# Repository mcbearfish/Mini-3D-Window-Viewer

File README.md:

# 3D Window Project

## About
This is a developmental project intended to refresh my skills on designing and programming an STM32 microcontroller board. I chose a project scope that I believed would provide difficult circuit and programming challenges. I will document the development process in this README.<br />

If you stumble across this project feel free to use it for educational purposes. If you find errors or have questions about the circuit design or code feel free to reach out. Please cite this repository as a source if you plan to use it.<br />

## Table of Contents
- [Project Description](#project-description)
- [Demo Video](#demo-video)
- [Hardware / Software Used](#hardware--software-used)
- [Circuit Design](#circuit-design)
- [Box Design](#box-design)
- [Code Design](#code-design)
- [Notes on AI Assistance](#notes-on-ai-assistance)
- [Final Result](#final-result)

## Project Description
This project is the 3D Window Viewer.<br />

When placed on a flat surface, the device on startup will create a window into a 3D scene of a hammer (Boiler Up and Hail Purdue!). After startup, tilting and rotating the device updates the view of a 3D hammer while the virtual position remains anchored.<br />

This project uses I2C accelerometer, gyroscope, and magnetometer sensors to estimate device orientation in C. The original goal was IMU-only position tracking, but drift made that impractical, so I redesigned the demo around constrained motion. <br />

I designed my own custom STM32 development board and sensor board using KiCad Schematic and PCB Design Software. <br />

## Demo Video

## Hardware / Software Used
- STM32 microcontroller
- Custom STM32 main PCB
- Custom sensor PCB
- Accelerometer, gyroscope, and magnetometer over I2C
- LCD display
- KiCad for schematic and PCB design
- CLion IDE
- C firmware

## Circuit Design
#### STM32 Circuit
<br />
This STM32 chip was chosen for its large number of GPIO pins and processing capabilities.

#### Button
<br />
Simple button circuit to test user inputs.

#### LEDs
<br />
Used for initial testing and debugging.

#### Crystal Oscillator
<br />
Provides a highly stable, accurate, and precise frequency reference.

#### USB-C Connector
<br />
Provides power to the board.

#### Boot Switch
<br />
Reset switch.

#### Mounting Holes
<br />
Grounded pads to use for mounting and probe testing.

#### Pin Connectors
<br />

#### Buck Converter
<br />
Chosen to smooth 5V to 3.3V for STM32 chip and sensors.

#### Accelerometer and Gyroscope
<br />
Chosen to estimate device orientation and motion. IMU-only position tracking was tested, but drift made it impractical for this version.

#### Magnetometer
<br />
Chosen to improve heading estimation and help correct gyro drift over time.

#### Pin Connector
<br />

#### Mounting Holes
<br />

#### Notes
I found Google's Gemini AI tool to be extremely helpful during this design process. Especially with mapping the pinout of the display to STM32. I used a cheap knockoff with no documentation and poor pinout labels. In the future may need to remap pins if display fails to work. See ARSensors project for second Board meant to connect sensors to this main board.<br />

Manufacturing files can be found for each board in this repository.<br />

#### Main PCB
<br />

<br />

<br />

<br />

#### Sensors PCB
<br />

<br />

<br />

<br />

#### Design Process
Designing my first board in almost 4 years was a great experience. In the workspace I have been living in a more software heavy environment. I found this project to be a great refresher of my skills.<br />

I found the initial research phase to be quite enjoyable and straightforward. I easily identified the types of sensors, display, and STM32 chip I thought would be capable for the performance I wanted. Now that I identified the key components it was time to begin creating the schematic.<br />

I quickly realized this was a larger challenge than my senior design project. Although I took a significant part in the circuit design, I realized how beneficial it was having a team of 4 people in multiple disciplines. The components I selected for this project were much more sophisticated than what was chosen for the senior design project. I was honestly a little overwhelmed at the start. I had to take my time and started to break components down. I started with the most important part, the STM32 chip. <br />

For the STM32 I first connected any power related pins and decoupling capacitors. Then I used the STM32CubeMX tool to assign pinouts. I knew between the display and other peripherals I needed a lot of pins, so I started by making sure the chip was capable of supporting them all. Once I verified the chip was capable I began connecting components. The most critical was the USB-C connector, which flashes code onto the chip. The USB-C will also provide power to the whole system. I spent quite a bit of time researching possible power designs. The USB-C provides 5V and I need 3.3V for the STM32 and sensors. I eventually decided on a synchronous buck converter because it would provide an efficient and stable step down from 5V to 3.3V. The display needs 5V, so I decided on a simple low-pass filter because it would provide a clean signal and I have experience with designing those on circuit boards in the past.<br />

Next I added the sensors. I found the datasheets to be extremely helpful. The design process was made much easier by following the typical application circuits that they detailed. Then I added the display, button, and some LEDs. The extra LEDs and button will be useful at the start of programming to make sure the board can properly run code and debug. Lastly I added a connector for debug pins.<br />

Now that I had a schematic to follow I moved onto the PCB layout. This portion was much more difficult than expected. It was at this point I had to take into account physical and cost restrictions. JLCPCB was my choice of board manufacturer. To minimize costs I decided on a 2 layer board, which gave me a lot of physical trace constraints.  Also, since the sensors are a bit costly, I decided to move them to a second circuit board to save on future costs. With these new challenges I had to go back to my schematic and STM32CubeMX. Unfortunately I was not able to place my STM32 pinouts more conveniently to minimize trace crossovers. At this point I decided to go with a more generic pin layout that I can wire with some 2.54mm connectors to minimize my trace lengths and crossovers. In the future I will look at more layered boards or other STM32 chips as potential solutions.<br />

To minimize costs on JLCPCB I tried to identify basic parts in the JLCPCB library. Not all parts selected were in that and drove up the cost (~$3 per part not in the basic library). In the future I will place more emphasis on this to lower my costs.<br />

Major credit to Phil's Lab PCB Design video: https://www.youtube.com/watch?v=aVUqaB0IMh4. This was a great refresher on circuit board design and I highly recommend his channel.<br />

#### Soldering and Assembly
When ordering the board I decided that to save on costs to I would hand solder some of the components. This involved things the STM32 chip, USB-C connector, asynchronous buck converter, buttons, and pins. I felt this was a great skill refresher. I took it slow and steady. I started with easier items like the pins and buttons to get back into the flow of things. The picture below is from right before I went to solder the STM chip.<br />
<br />

I bought a cheap soldering station and found it pretty useful when adding the smaller components. In the picture below you can see a cheaper soldering iron. I found this ok for the larger components but, I decided it was safer to spend the money and get a proper iron for the delicate items like the USB-C and STM32 chip.<br />
<br />

### Box Design
I bought a simple project box and placed the main board inside the box. I left the sensor board on top along with the display to keep them on the same level.

## Code Design
#### Initial Project Scope
The initial goal of the project was to use the IMU sensors to track the 3D coordinates of the device so that it could act as a camera. The camera would then be able to view a 3D object fixed in space from all angles and get closer or farther away.<br />

#### Limitations of IMU Sensors
While prototyping I found that it was not feasible to use the IMU sensors alone for positional tracking. The significant position drift was too much to overcome, even with adjusting bias in the Kalman filter parameters. I also tested the individual sensors to check for noise and bias. Surprisingly, these cheaper sensors performed quite well. The accelerometer did display the most noise. I believe this was due to environmental sensitivities. Testing was performed on my desk and away from any electronics, this however does not guarantee a perfectly still environment. <br />

Since position is calculated by integrating acceleration twice, even with tiny errors, the positional data errors grew massive. The estimated position drifted so quickly that the 3D object would only remain visible for a split second. I determined this was unusable and decided to change scope. <br />

#### Redesign
I decided to pivot the project and try to get the most out of the current setup. I decided to simulate the camera view of the 3D object where moving and tilting the box changes camera view direction realistically, but position is anchored. <br />

#### Code Flow
The main program initializes the board, sensors, sensor fusion, and 3D engine before entering the main loop. In the loop, new sensor data is read and passed into the sensor fusion algorithm. This project uses an Extended Kalman Filter, which fuses gyroscope, accelerometer, and magnetometer data into a stable orientation estimate. That orientation estimate is then used to update the rendered 3D object and draw the pose overlay.<br />
```
main()
|
+-- HAL_Init()
+-- SystemClock_Config()
+-- MX_GPIO_Init()
+-- MX_FMC_Init()
+-- I2C_Bus_Reset()
+-- MX_I2C1_Init()
|
+-- Engine3D_Init()
|   \-- GPU_Init()
|
+-- Sensors_Init()
+-- Sensors_ShowStartupCountdown()
+-- Sensors_Calibrate()
+-- Sensors_ShowInstructionScreen()
+-- Sensors_GetReferenceFrame()
+-- EKF_Init()
+-- EKF_SetReference()
|
\-- while (1)
    +-- Sensors_Read()
    +-- EKF_Predict()
    +-- EKF_Update()
    +-- ComputeSpinCommands()
    +-- IntegrateQuat()
    +-- IsStableForReset()
    |   \-- maybe ResetObjectOrientation()
    +-- QuaternionToEulerDegrees()
    +-- Engine3D_SetCameraPose()
    +-- Engine3D_SetObjectRotation()
    +-- Engine3D_PrepareFrame()
    +-- GPU_Render(Engine3D_DrawScene)
    \-- DrawPoseOverlay()
```

## Notes on AI Assistance
Portions of the firmware were developed with assistance from AI tools, including OpenAI Codex and Google's Gemini. I used these tools to help generate code structure, debug embedded issues and tune parts of the sensor-fusion pipeline. All AI-assisted code was reviewed, tested, and modified by me before being included in the final project. <br />

I found Codex especially useful for working through embedded C issues and code organization. Gemini was useful during early design exploration, especially for brainstorming and pin-mapping support, but I had to review its output carefully because it sometimes suggested larger code changes than intended. <br />

## Final Result
The final device renders a wireframe 3D hammer on the LCD. After startup calibration, tilting or rotating the physical box updates the rendered view in real time. The device uses IMU sensor fusion for orientation estimation while keeping virtual position constrained to avoid IMU drift. <br />

This project was great for refreshing my bare-metal embedded skills. Making a device and writing code that brings it to life is always a joy. The next project should hopefully move faster now that I have regained familiarity with the whole process.

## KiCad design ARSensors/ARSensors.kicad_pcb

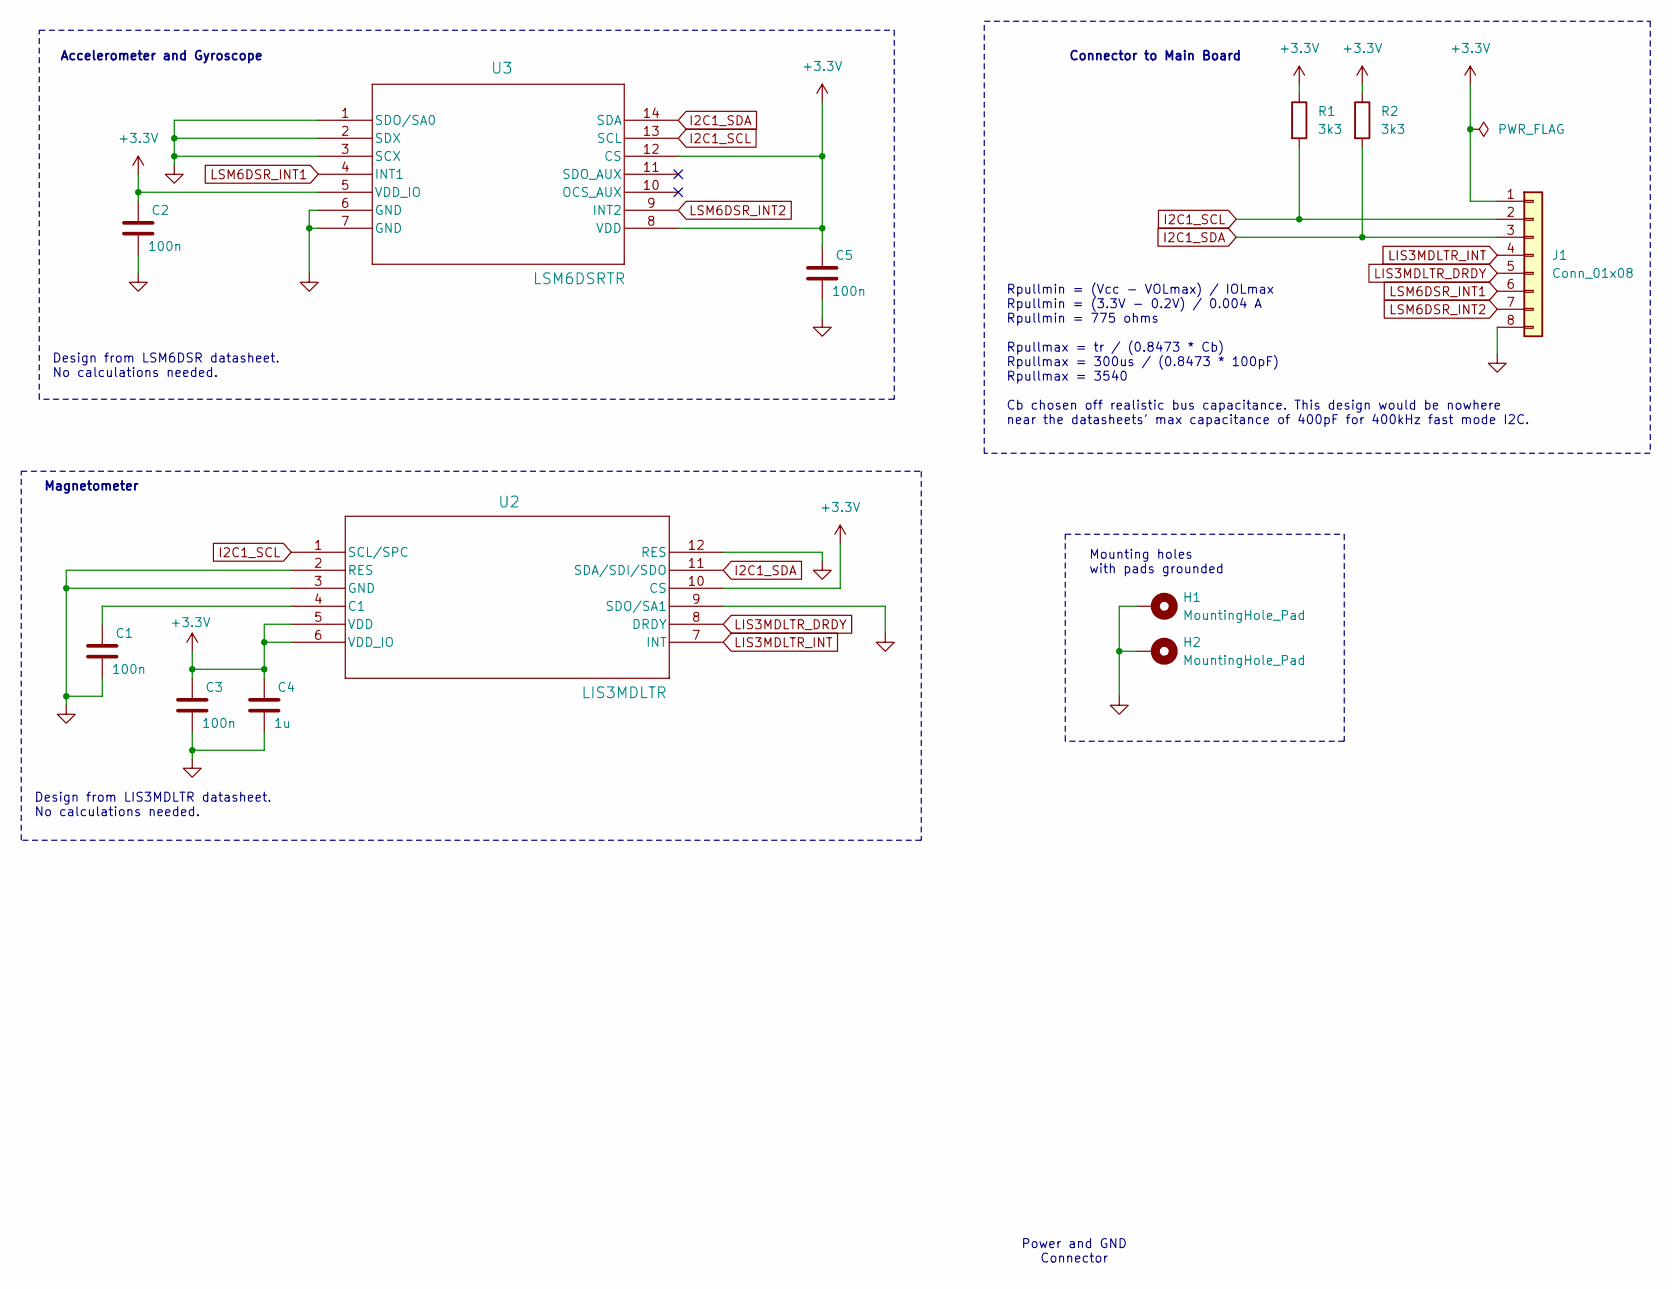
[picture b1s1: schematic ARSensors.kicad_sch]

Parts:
C1, C2, C3, C5: 100n; C_0402_1005Metric
C4: 1u; C_0402_1005Metric
H1, H2: MountingHole_Pad; MountingHole_4.3mm_M4_Pad_Via
J1: Conn_01x08; PinHeader_1x08_P2.54mm_Vertical
R1, R2: 3k3; R_0603_1608Metric
U2: LIS3MDLTR; LGA-12_2X2X1_STM
U3: LSM6DSRTR; LGA-14L_2P5X3X0P83_STM

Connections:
+3.3V: C2.1, C3.1, C4.1, C5.1, J1.1, R1.1, R2.1, U2.5 (VDD), U2.6 (VDD_IO), U2.10 (CS), U3.5 (VDD_IO), U3.8 (VDD), U3.12 (CS)
GND: C1.2, C2.2, C3.2, C4.2, C5.2, H1.1, H2.1, J1.8, U2.2 (RES), U2.3 (GND), U2.9 (SDO/SA1), U2.12 (RES), U3.1 (SDO/SA0), U3.2 (SDX), U3.3 (SCX), U3.6 (GND), U3.7 (GND)
I2C1_SCL: J1.2, R1.2, U2.1 (SCL/SPC), U3.13 (SCL)
I2C1_SDA: J1.3, R2.2, U2.11 (SDA/SDI/SDO), U3.14 (SDA)
LIS3MDLTR_DRDY: J1.5, U2.8 (DRDY)
LIS3MDLTR_INT: J1.4, U2.7 (INT)
LSM6DSR_INT1: J1.6, U3.4 (INT1)
LSM6DSR_INT2: J1.7, U3.9 (INT2)
unnamed: C1.1, U2.4 (C1)

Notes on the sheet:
Rpullmin = (Vcc - VOLmax) / IOLmax Rpullmin = (3.3V - 0.2V) / 0.004 A Rpullmin = 775 ohms Rpullmax = tr / (0.8473 * Cb) Rpullmax = 300us / (0.8473 * 100pF) Rpullmax = 3540 Cb chosen off realistic bus capacitance. This design would be nowhere near the datasheets' max capacitance of 400pF for 400kHz 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
Design from LIS3MDLTR datasheet. No calculations needed.
Mounting holes with pads grounded
Design from LSM6DSR datasheet. No calculations needed.
Power and GND Connector
Connector to Main Board
Magnetometer
Accelerometer and Gyroscope

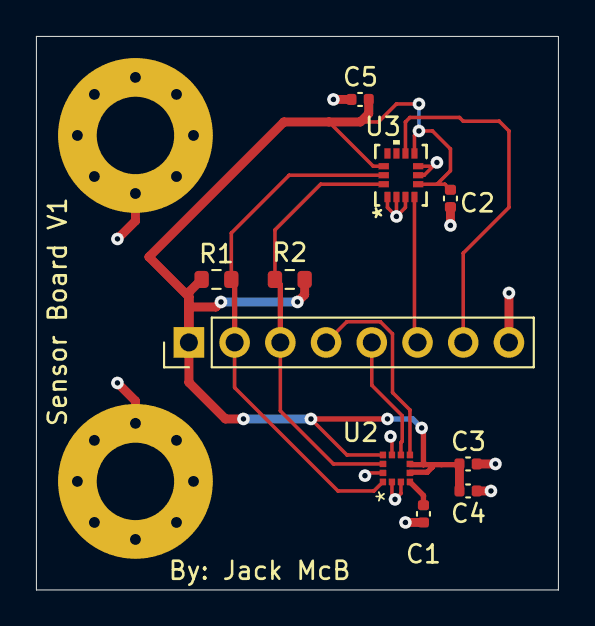
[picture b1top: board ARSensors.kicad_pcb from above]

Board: 2 copper layers, 29.0 x 30.8 mm, 12 parts (0 on the bottom side), 9 nets.

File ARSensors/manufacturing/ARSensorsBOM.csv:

Designator,Comment,Footprint,JLCPCB Part #
"C1,C2,C3,C5",100n,Capacitor_SMD:C_0402_1005Metric,C1525
C4,1u,Capacitor_SMD:C_0402_1005Metric,C52923
"R1,R2",3k3,Resistor_SMD:R_0603_1608Metric,C22978
U2,LIS3MDLTR,footprints1:LGA-12_2X2X1_STM,C478483
U3,LSM6DSRTR,footprints:LGA-14L_2P5X3X0P83_STM,C784817

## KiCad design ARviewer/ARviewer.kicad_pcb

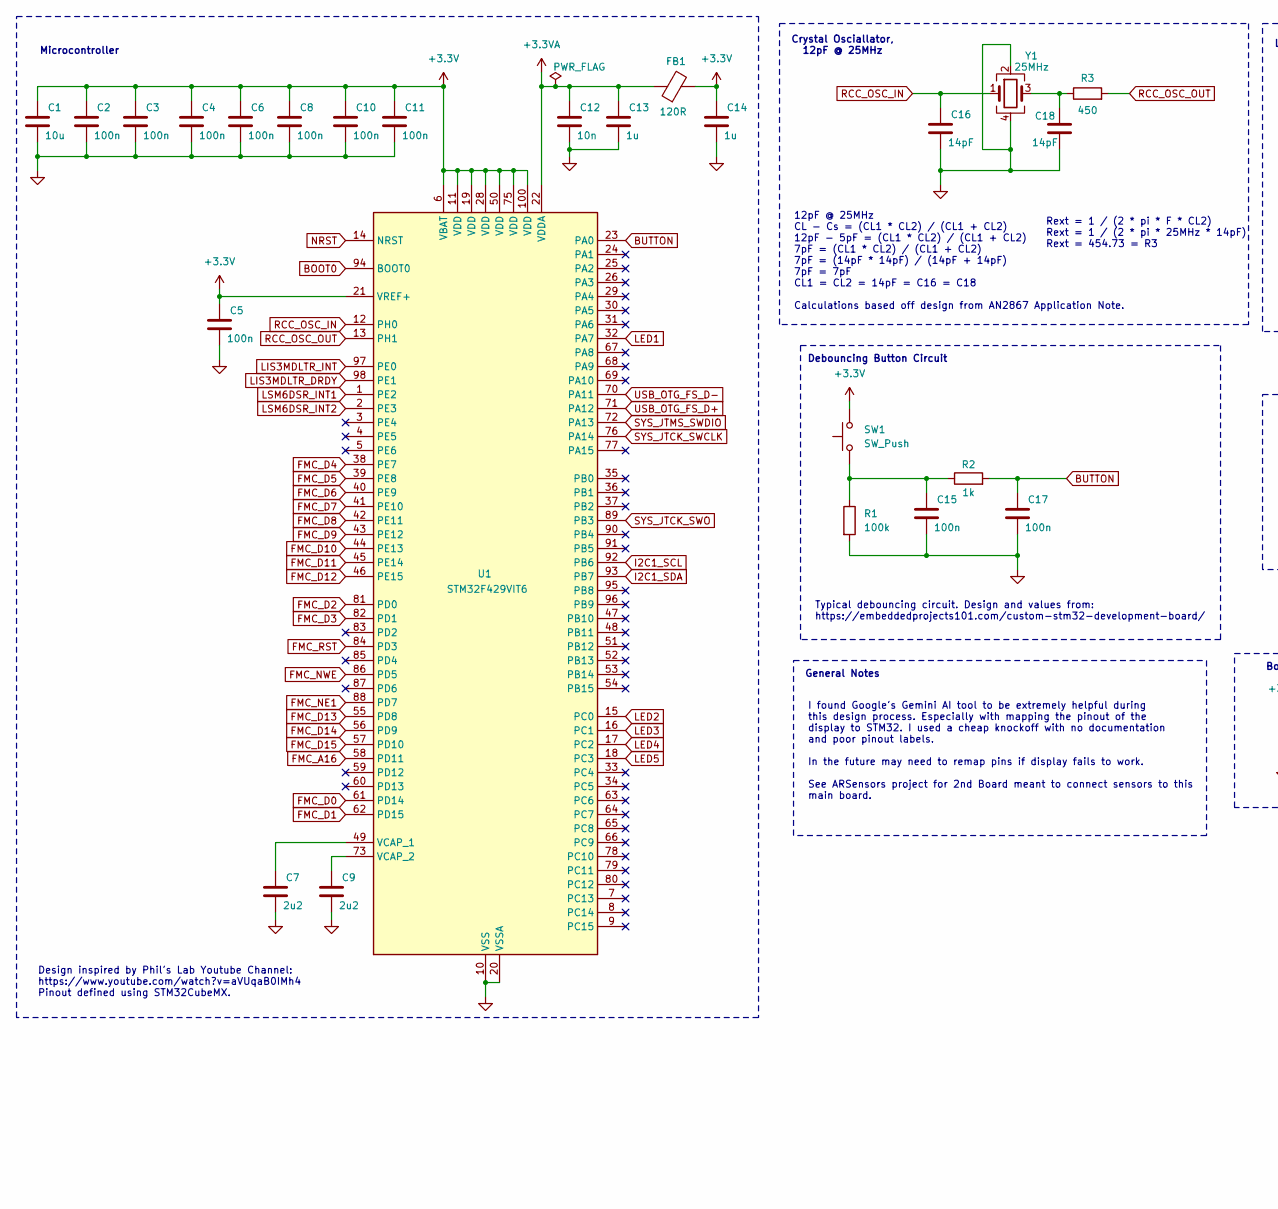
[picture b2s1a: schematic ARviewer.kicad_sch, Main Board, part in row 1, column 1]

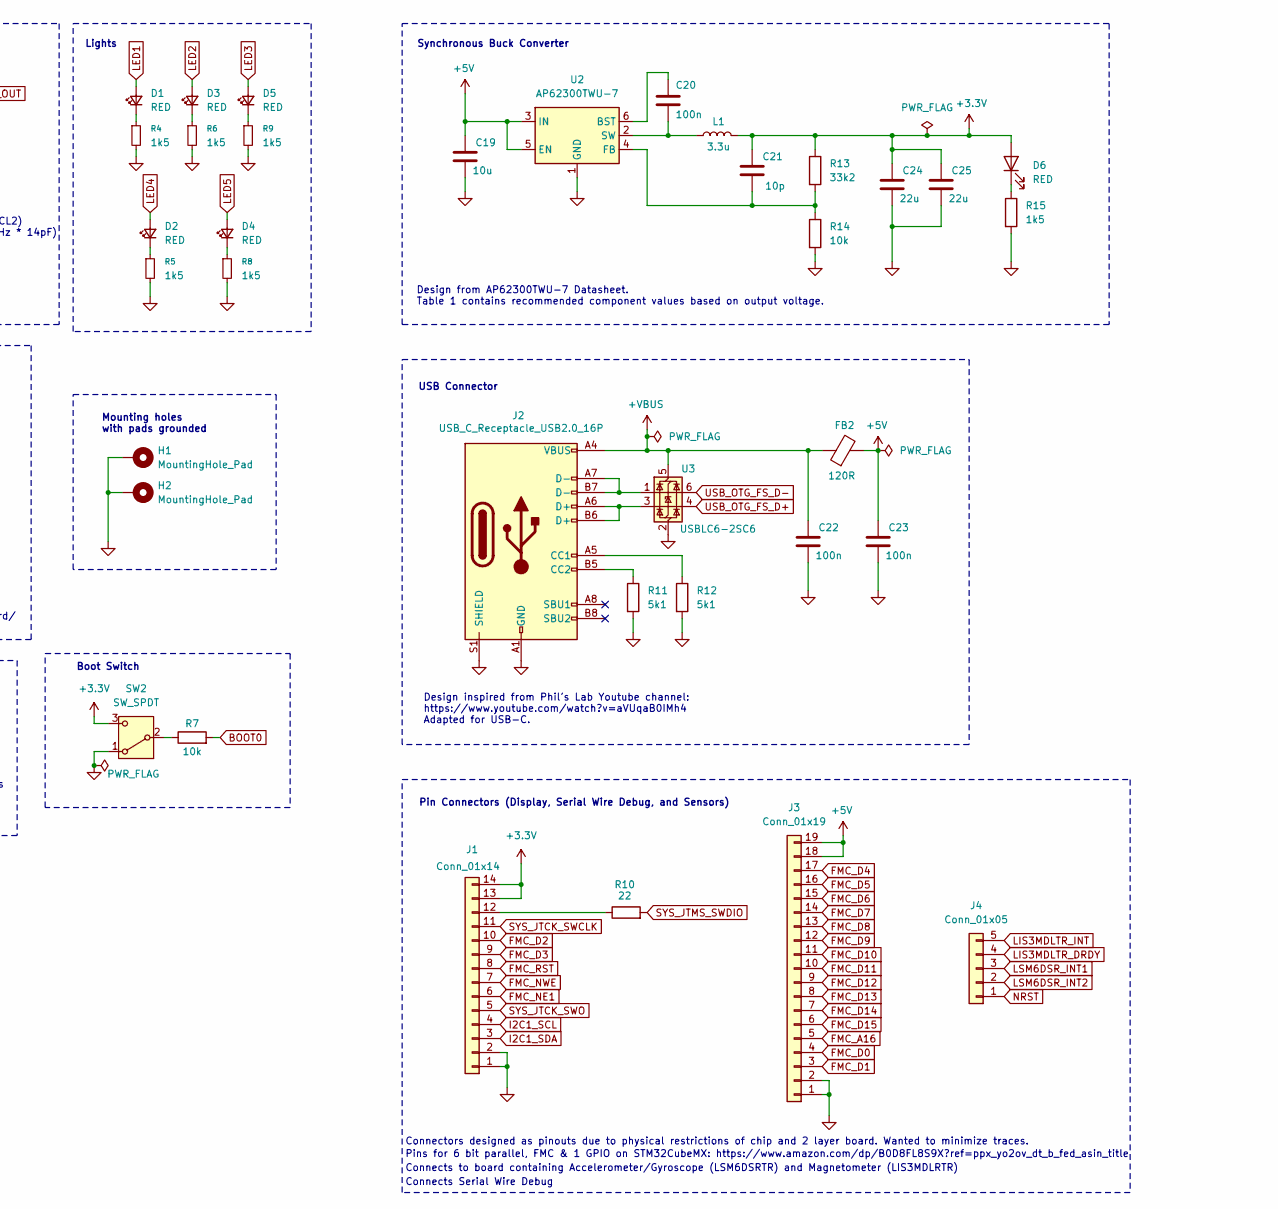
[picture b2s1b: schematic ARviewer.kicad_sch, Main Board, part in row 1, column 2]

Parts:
C1, C19: 10u; C_0603_1608Metric
C2, C3, C4, C5, C6, C8, C10, C11, C15, C17, C20, C22, C23: 100n; C_0402_1005Metric
C7, C9: 2u2; C_0402_1005Metric
C12: 10n; C_0402_1005Metric
C13, C14: 1u; C_0402_1005Metric
C16, C18: 14pF; C_0402_1005Metric
C21: 10p; C_0402_1005Metric
C24, C25: 22u; C_0805_2012Metric
D1, D2, D3, D4, D5, D6: RED; LED_0603_1608Metric
FB1, FB2: 120R; L_0603_1608Metric
H1, H2: MountingHole_Pad; MountingHole_4.3mm_M4_Pad_Via
J1: Conn_01x14; PinHeader_1x14_P2.54mm_Vertical
J2: USB_C_Receptacle_USB2.0_16P; USB_C_Receptacle_GCT_USB4105-xx-A_16P_TopMnt_Horizontal
J3: Conn_01x19; PinHeader_1x19_P2.54mm_Vertical
J4: Conn_01x05; PinHeader_1x05_P2.54mm_Vertical
L1: 3.3u; L_6.3x6.3_H3
R1: 100k; R_0805_2012Metric
R2: 1k; R_0603_1608Metric
R3: 450; R_0402_1005Metric
R4, R5, R6, R8, R9, R15: 1k5; R_0603_1608Metric
R7: 10k; R_0402_1005Metric
R10: 22; R_0603_1608Metric
R11, R12: 5k1; R_0603_1608Metric
R13: 33k2; R_0805_2012Metric
R14: 10k; R_0805_2012Metric
SW1: SW_Push; SW_PUSH_6mm
SW2: SW_SPDT; SW_SPDT_PCM12
U1: STM32F429VIT6; LQFP-100_14x14mm_P0.5mm
U2: AP62300TWU-7; TSOT-23-6
U3: USBLC6-2SC6; SOT-23-6
Y1: 25MHz; Crystal_SMD_3225-4Pin_3.2x2.5mm

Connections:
+3.3V: C1.1, C2.1, C3.1, C4.1, C5.1, C6.1, C8.1, C10.1, C11.1, C14.1, C21.1, C24.1, C25.1, D6.2 (A), FB1.2, J1.13, J1.14, L1.2, R13.1, SW1.2, SW2.3 (C), U1.6 (VBAT), U1.11 (VDD), U1.19 (VDD), U1.21 (VREF+), U1.28 (VDD), U1.50 (VDD), U1.75 (VDD), U1.100 (VDD)
+3.3VA: C12.1, C13.1, FB1.1, U1.22 (VDDA)
+5V: C19.1, C23.1, FB2.2, J3.18, J3.19, U2.3 (IN), U2.5 (EN)
+VBUS: C22.1, FB2.1, J2.A4 (VBUS), J2.A9 (VBUS), J2.B4 (VBUS), J2.B9 (VBUS), U3.5 (VBUS)
BOOT0: R7.2, U1.94 (BOOT0)
BUTTON: C17.1, R2.2, U1.23 (PA0)
FMC_A16: J3.5, U1.58 (PD11)
FMC_D0: J3.4, U1.61 (PD14)
FMC_D1: J3.3, U1.62 (PD15)
FMC_D2: J1.10, U1.81 (PD0)
FMC_D3: J1.9, U1.82 (PD1)
FMC_D4: J3.17, U1.38 (PE7)
FMC_D5: J3.16, U1.39 (PE8)
FMC_D6: J3.15, U1.40 (PE9)
FMC_D7: J3.14, U1.41 (PE10)
FMC_D8: J3.13, U1.42 (PE11)
FMC_D9: J3.12, U1.43 (PE12)
FMC_D10: J3.11, U1.44 (PE13)
FMC_D11: J3.10, U1.45 (PE14)
FMC_D12: J3.9, U1.46 (PE15)
FMC_D13: J3.8, U1.55 (PD8)
FMC_D14: J3.7, U1.56 (PD9)
FMC_D15: J3.6, U1.57 (PD10)
FMC_NE1: J1.6, U1.88 (PD7)
FMC_NWE: J1.7, U1.86 (PD5)
FMC_RST: J1.8, U1.84 (PD3)
GND: C1.2, C2.2, C3.2, C4.2, C5.2, C6.2, C7.2, C8.2, C9.2, C10.2, C11.2, C12.2, C13.2, C14.2, C15.2, C16.2, C17.2, C18.2, C19.2, C22.2, C23.2, C24.2, C25.2, H1.1, H2.1, J1.1, J1.2, J2.A1 (GND), J2.A12 (GND), J2.B1 (GND), J2.B12 (GND), J2.S1 (SHIELD), J3.1, J3.2, R1.2, R4.2, R5.2, R6.2, R8.2, R9.2, R11.2, R12.2, R14.2, R15.2, SW2.1 (A), U1.10 (VSS), U1.20 (VSSA), U1.27 (VSS), U1.74 (VSS), U1.99 (VSS), U2.1 (GND), U3.2 (GND), Y1.2, Y1.4
I2C1_SCL: J1.4, U1.92 (PB6)
I2C1_SDA: J1.3, U1.93 (PB7)
LED1: D1.2 (A), U1.32 (PA7)
LED2: D3.2 (A), U1.15 (PC0)
LED3: D5.2 (A), U1.16 (PC1)
LED4: D2.2 (A), U1.17 (PC2)
LED5: D4.2 (A), U1.18 (PC3)
LIS3MDLTR_DRDY: J4.4, U1.98 (PE1)
LIS3MDLTR_INT: J4.5, U1.97 (PE0)
LSM6DSR_INT1: J4.3, U1.1 (PE2)
LSM6DSR_INT2: J4.2, U1.2 (PE3)
NRST: J4.1, U1.14 (NRST)
unnamed: C15.1, R1.1, R2.1, SW1.1
unnamed: C18.1, R3.1, Y1.3
unnamed: D1.1 (K), R4.1
unnamed: D2.1 (K), R5.1
unnamed: D3.1 (K), R6.1
unnamed: D4.1 (K), R8.1
unnamed: D5.1 (K), R9.1
unnamed: D6.1 (K), R15.1
unnamed: J1.12, R10.1
unnamed: J2.A5 (CC1), R12.1
unnamed: J2.B5 (CC2), R11.1
unnamed: J2.A6 (D+), J2.B6 (D+), U3.3 (I/O2)
unnamed: J2.A7 (D-), J2.B7 (D-), U3.1 (I/O1)
unnamed: R7.1, SW2.2 (B)
unnamed: C7.1, U1.49 (VCAP_1)
unnamed: C9.1, U1.73 (VCAP_2)
unnamed: C20.1, U2.6 (BST)
unnamed: C21.2, R13.2, R14.1, U2.4 (FB)
unnamed: C20.2, L1.1, U2.2 (SW)
RCC_OSC_IN: C16.1, U1.12 (PH0), Y1.1
RCC_OSC_OUT: R3.2, U1.13 (PH1)
SYS_JTCK_SWCLK: J1.11, U1.76 (PA14)
SYS_JTCK_SWO: J1.5, U1.89 (PB3)
SYS_JTMS_SWDIO: R10.2, U1.72 (PA13)
USB_OTG_FS_D+: U1.71 (PA12), U3.4 (I/O2)
USB_OTG_FS_D-: U1.70 (PA11), U3.6 (I/O1)

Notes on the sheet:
Design inspired from Phil's Lab Youtube channel: https://www.youtube.com/watch?v=aVUqaB0IMh4 Adapted for USB-C.
Synchronous Buck Converter
Mounting holes with pads grounded
Typical debouncing circuit. Design and values from: https://embeddedprojects101.com/custom-stm32-development-board/
Design inspired by Phil's Lab Youtube Channel: https://www.youtube.com/watch?v=aVUqaB0IMh4 Pinout defined using STM32CubeMX.
12pF @ 25MHz CL - Cs = (CL1 * CL2) / (CL1 + CL2) 12pF - 5pF = (CL1 * CL2) / (CL1 + CL2) 7pF = (CL1 * CL2) / (CL1 + CL2) 7pF = (14pF * 14pF) / (14pF + 14pF) 7pF = 7pF CL1 = CL2 = 14pF = C16 = C18 Calculations based off design from AN2867 Application Note.
Microcontroller
Design from AP62300TWU-7 Datasheet. Table 1 contains recommended component values based on output voltage.
I found Google's Gemini AI tool to be extremely helpful during this design process. Especially with mapping the pinout of the display to STM32. I used a cheap knockoff with no documentation and poor pinout labels. In the future may need to remap pins if display fails to work. See ARSensors project 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
Boot Switch
Crystal Osciallator, 12pF @ 25MHz
Pin Connectors (Display, Serial Wire Debug, and Sensors)
Pins for 6 bit parallel, FMC & 1 GPIO on STM32CubeMX: https://www.amazon.com/dp/B0D8FL8S9X?ref=ppx_yo2ov_dt_b_fed_asin_title
General Notes
Connectors designed as pinouts due to physical restrictions of chip and 2 layer board. Wanted to minimize traces.
Debouncing Button Circuit
USB Connector
Connects to board containing Accelerometer/Gyroscope (LSM6DSRTR) and Magnetometer (LIS3MDLRTR)
Lights
Connects Serial Wire Debug
Rext = 1 / (2 * pi * F * CL2) Rext = 1 / (2 * pi * 25MHz * 14pF) Rext = 454.73 = R3

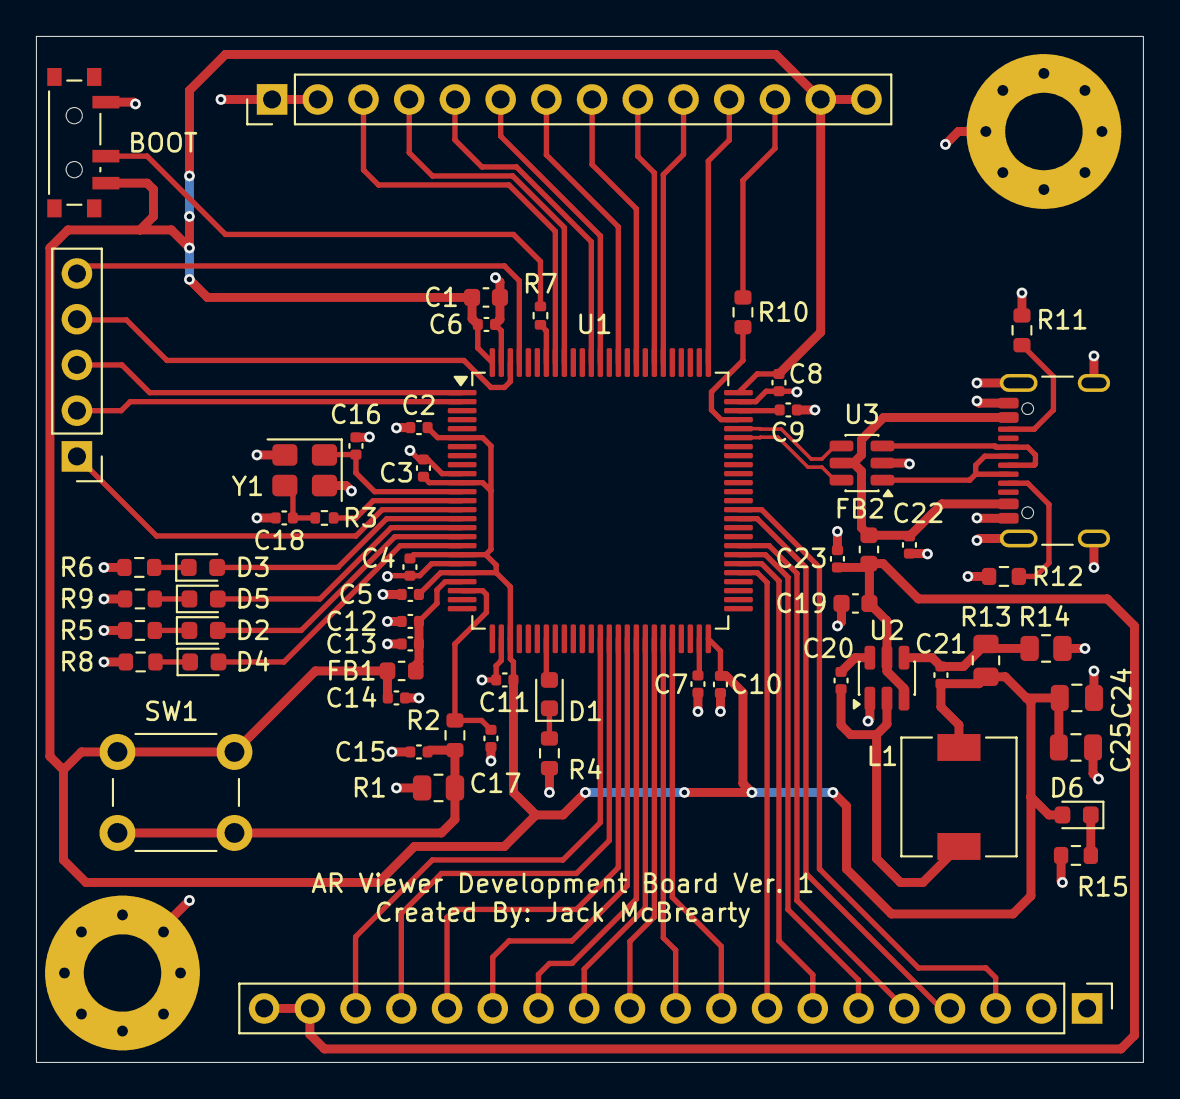
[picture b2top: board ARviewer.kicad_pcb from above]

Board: 2 copper layers, 61.5 x 57.0 mm, 61 parts (0 on the bottom side), 65 nets.

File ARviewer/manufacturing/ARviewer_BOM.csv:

Comment,Designator,Footprint,JLCPCB Part #
10u,"C1,C19",Capacitor_SMD:C_0603_1608Metric,C19702
100n,"C2,C3,C4,C5,C6,C8,C10,C11,C15,C17,C20,C22,C23",Capacitor_SMD:C_0402_1005Metric,C1525
2u2,"C7,C9",Capacitor_SMD:C_0402_1005Metric,C12530
10n,C12,Capacitor_SMD:C_0402_1005Metric,C15195
1u,"C13,C14",Capacitor_SMD:C_0402_1005Metric,C52923
14pF,"C16,C18",Capacitor_SMD:C_0402_1005Metric,C458857
10p,C21,Capacitor_SMD:C_0402_1005Metric,C32949
22u,"C24,C25",Capacitor_SMD:C_0805_2012Metric,C45783
GREEN,"D1,D6",LED_SMD:LED_0603_1608Metric,C2286
ORANGE,D2,LED_SMD:LED_0603_1608Metric,C2286
BLUE,D3,LED_SMD:LED_0603_1608Metric,C2286
YELLOW,D4,LED_SMD:LED_0603_1608Metric,C2286
RED,D5,LED_SMD:LED_0603_1608Metric,C2286
120R,"FB1,FB2",Inductor_SMD:L_0603_1608Metric,C14709
USB_C_Receptacle_USB2.0_16P,J2,Connector_USB:USB_C_Receptacle_GCT_USB4105-xx-A_16P_TopMnt_Horizontal,C3020560
3.3u,L1,Inductor_SMD:L_6.3x6.3_H3,C206311
100k,R1,Resistor_SMD:R_0805_2012Metric,C149504
1k,R2,Resistor_SMD:R_0603_1608Metric,C21190
450,R3,Resistor_SMD:R_0402_1005Metric,C159027
1k5,"R4,R5,R6,R8,R9,R15",Resistor_SMD:R_0603_1608Metric,C22843
10k,R7,Resistor_SMD:R_0402_1005Metric,C25744
22,R10,Resistor_SMD:R_0603_1608Metric,C23345
5k1,"R11,R12",Resistor_SMD:R_0603_1608Metric,C23186
33k2,R13,Resistor_SMD:R_0805_2012Metric,C37252
10k,R14,Resistor_SMD:R_0805_2012Metric,C17414
SW_Push,SW1,Button_Switch_THT:SW_PUSH_6mm,C557623
SW_SPDT,SW2,Button_Switch_SMD:SW_SPDT_PCM12,C221841
STM32F429VIT6,U1,Package_QFP:LQFP-100_14x14mm_P0.5mm,C92002
AP62300TWU-7,U2,Package_TO_SOT_SMD:TSOT-23-6,C1883519
USBLC6-2SC6,U3,Package_TO_SOT_SMD:SOT-23-6,C7519
25MHz,Y1,Crystal:Crystal_SMD_3225-4Pin_3.2x2.5mm,C9006

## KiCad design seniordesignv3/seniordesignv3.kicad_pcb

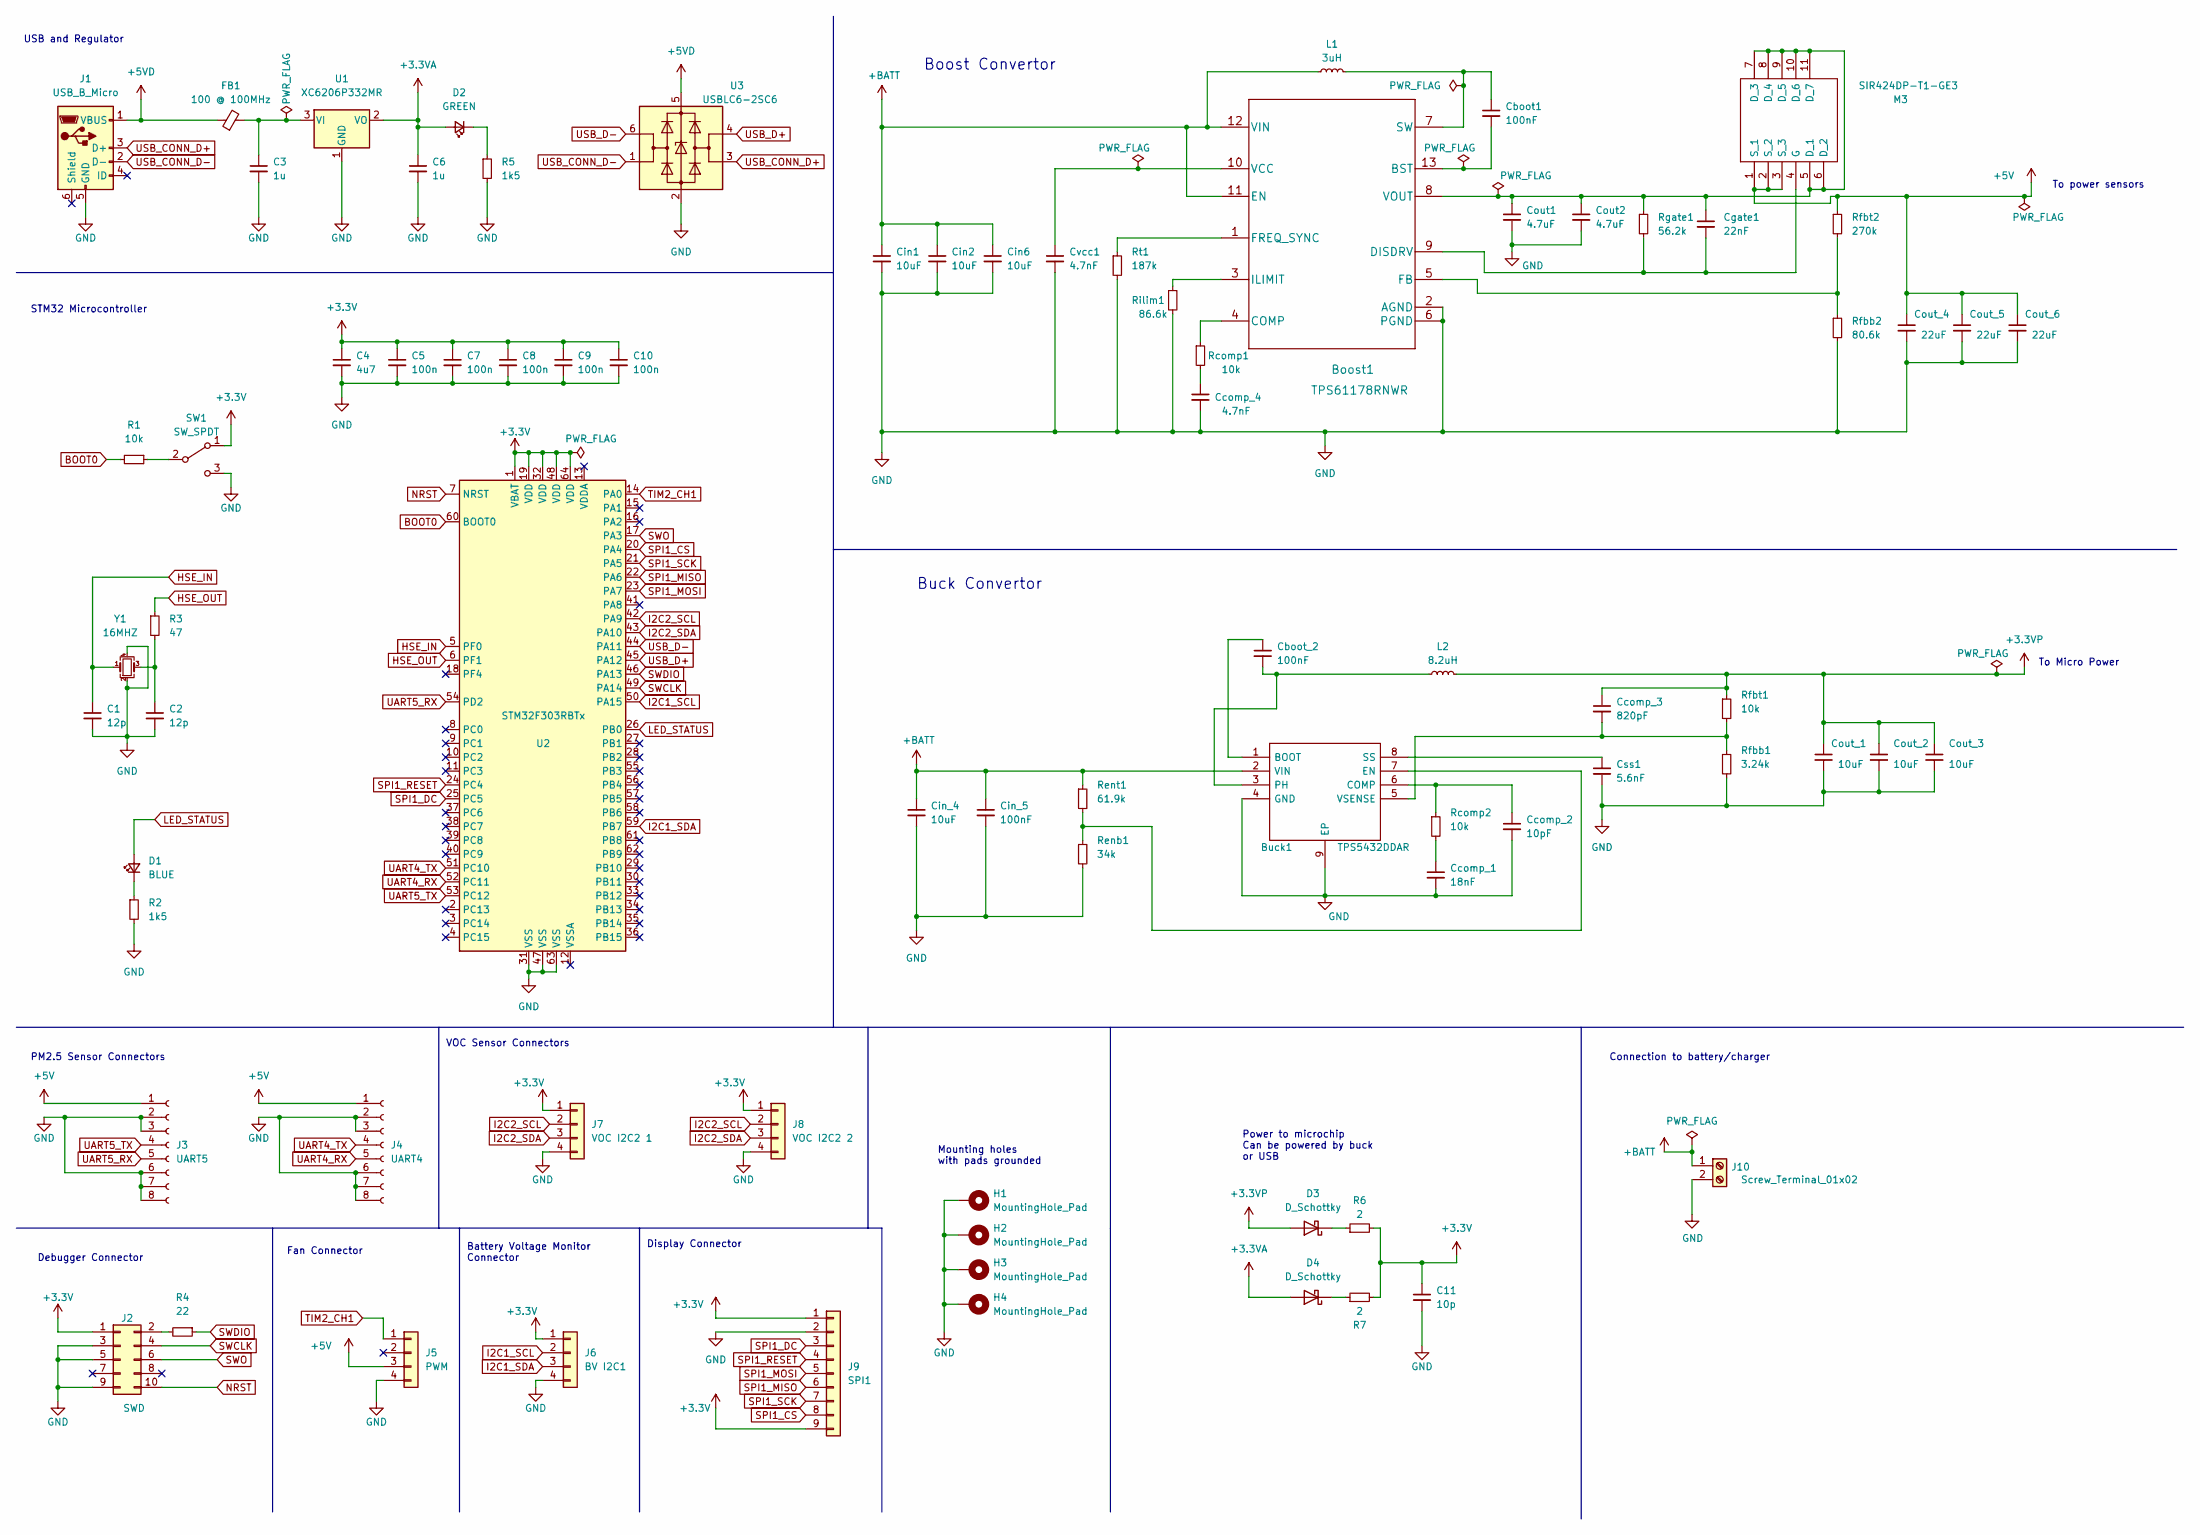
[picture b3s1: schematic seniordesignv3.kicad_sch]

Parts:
Boost1: TPS61178RNWR; RNW0013A
Buck1: TPS5432DDAR; SOIC127P600X170-9N; Manufacturer_Part_Number TPS5432DDAR; Mouser Part Number 595-TPS5432DDAR
C1, C2: 12p; C_0402_1005Metric; LCSC Part # C1547
C3, C6: 1u; C_0402_1005Metric; LCSC Part # C52923
C4: 4u7; C_0603_1608Metric; LCSC Part # C19666
C5, C7, C8, C9, C10: 100n; C_0402_1005Metric; LCSC Part # C307331
C11: 10p; C_0603_1608Metric; LCSC Part # C1634
Cboot1: 100nF; C_0805_2012Metric
Cboot_2: 100nF; C_0805_2012Metric
Ccomp_1: 18nF; C_0603_1608Metric
Ccomp_2: 10pF; C_0805_2012Metric
Ccomp_3: 820pF; C_0402_1005Metric
Ccomp_4: 4.7nF; C_0805_2012Metric
Cgate1: 22nF; C_0805_2012Metric
Cin1, Cin2, Cin6: 10uF; C_0805_2012Metric
Cin_4: 10uF; C_0805_2012Metric
Cin_5: 100nF; C_0805_2012Metric
Cout1, Cout2: 4.7uF; C_0805_2012Metric
Cout_1, Cout_2, Cout_3: 10uF; C_0805_2012Metric
Cout_4, Cout_5, Cout_6: 22uF; C_0805_2012Metric
Css1: 5.6nF; C_0805_2012Metric
Cvcc1: 4.7nF; C_0805_2012Metric
D1: BLUE; LED_0603_1608Metric; LCSC Part # C72041
D2: GREEN; LED_0603_1608Metric; LCSC Part # C72043
D3, D4: D_Schottky; D_SOD-123; LCSC Part # C8598
FB1: 100 @ 100MHz; L_0805_2012Metric; LCSC Part # C1017
H1, H2, H3, H4: MountingHole_Pad; MountingHole_4.3mm_M4_Pad_Via
J1: USB_B_Micro; USB_Micro-B_Molex-105017-0001
J2: SWD; PinHeader_2x05_P2.54mm_Vertical
J3: UART5; Molex_PicoBlade_53261-0871_1x08-1MP_P1.25mm_Horizontal
J4: UART4; Molex_PicoBlade_53261-0871_1x08-1MP_P1.25mm_Horizontal
J5: PWM; PinHeader_1x04_P2.54mm_Vertical
J6: BV I2C1; PinHeader_1x04_P2.54mm_Vertical
J7: VOC I2C2 1; PinHeader_1x04_P2.54mm_Vertical
J8: VOC I2C2 2; PinHeader_1x04_P2.54mm_Vertical
J9: SPI1; PinHeader_1x09_P2.54mm_Vertical
J10: Screw_Terminal_01x02; TerminalBlock_Phoenix_PT-1,5-2-3.5-H_1x02_P3.50mm_Horizontal
L1: 3uH; cjiang_IND
L2: 8.2uH; Wenshan_IND
M3: SIR424DP-T1-GE3; SI7852ADPT1GE3; Manufacturer_Part_Number SIR424DP-T1-GE3; Mouser Part Number 781-SIR424DP-GE3
R1: 10k; R_0402_1005Metric; LCSC Part # C25744
R2, R5: 1k5; R_0603_1608Metric; LCSC Part # C22843
R3: 47; R_0402_1005Metric; LCSC Part # C25792
R4: 22; R_0402_1005Metric; LCSC Part # C25092
R6, R7: 2; R_0603_1608Metric; LCSC Part # C22977
Rcomp1, Rcomp2: 10k; R_0805_2012Metric
Renb1: 34k; R_0805_2012Metric
Rent1: 61.9k; R_0805_2012Metric
Rfbb1: 3.24k; R_0805_2012Metric
Rfbb2: 80.6k; R_0805_2012Metric
Rfbt1: 10k; R_0805_2012Metric
Rfbt2: 270k; R_0805_2012Metric
Rgate1: 56.2k; R_0805_2012Metric
Rilim1: 86.6k; R_0805_2012Metric
Rt1: 187k; R_0805_2012Metric
SW1: SW_SPDT; SW_SPDT_PCM12
U1: XC6206P332MR; SOT-23; LCSC Part # C5446
U2: STM32F303RBTx; LQFP-64_10x10mm_P0.5mm; LCSC Part # C130453
U3: USBLC6-2SC6; SOT-23-6; LCSC Part # C2827654
Y1: 16MHZ; Crystal_SMD_3225-4Pin_3.2x2.5mm; LCSC Part # C13738

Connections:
+3.3VA: C6.1, D2.2 (A), D4.2 (A), U1.2 (VO)
+3.3VP: Ccomp_3.1, Cout_1.1, Cout_2.1, Cout_3.1, D3.2 (A), L2.2, Rfbt1.1
+3V3: C4.1, C5.1, C7.1, C8.1, C9.1, C10.1, C11.1, J2.1, J6.1, J7.1, J8.1, J9.1, J9.9, R6.2, R7.2, SW1.1 (A), U2.1 (VBAT), U2.19 (VDD), U2.32 (VDD), U2.48 (VDD), U2.64 (VDD)
+5V: Cout_4.1, Cout_5.1, Cout_6.1, J3.1, J4.1, J5.3, M3.1 (S_1), M3.2 (S_2), M3.3 (S_3), Rfbt2.1
+5VD: FB1.1, J1.1 (VBUS), U3.5 (VBUS)
+BATT: Boost1.11 (EN), Boost1.12 (VIN), Buck1.2 (VIN), Cin1.1, Cin2.1, Cin6.1, Cin_4.1, Cin_5.1, J10.1, L1.1, Rent1.1
BOOT0: R1.2, U2.60 (BOOT0)
GND: Boost1.2 (AGND), Boost1.6 (PGND), Buck1.4 (GND), Buck1.9 (EP), C1.2, C2.2, C3.2, C4.2, C5.2, C6.2, C7.2, C8.2, C9.2, C10.2, C11.2, Ccomp_1.2, Ccomp_2.2, Ccomp_4.2, Cin1.2, Cin2.2, Cin6.2, Cin_4.2, Cin_5.2, Cout1.2, Cout2.2, Cout_1.2, Cout_2.2, Cout_3.2, Cout_4.2, Cout_5.2, Cout_6.2, Css1.2, Cvcc1.2, H1.1, H2.1, H3.1, H4.1, J1.5 (GND), J2.3, J2.5, J2.9, J3.2, J3.3, J3.6, J3.7, J3.8, J4.2, J4.3, J4.6, J4.7, J4.8, J5.4, J6.4, J7.4, J8.4, J9.2, J10.2, R2.2, R5.2, Renb1.2, Rfbb1.2, Rfbb2.2, Rilim1.2, Rt1.2, SW1.3 (C), U1.1 (GND), U2.31 (VSS), U2.47 (VSS), U2.63 (VSS), U3.2 (GND), Y1.2, Y1.4
HSE_IN: C1.1, U2.5 (PF0), Y1.1
HSE_OUT: R3.1, U2.6 (PF1)
I2C1_SCL: J6.2, U2.50 (PA15)
I2C1_SDA: J6.3, U2.59 (PB7)
I2C2_SCL: J7.2, J8.2, U2.42 (PA9)
I2C2_SDA: J7.3, J8.3, U2.43 (PA10)
LED_STATUS: D1.2 (A), U2.26 (PB0)
NRST: J2.10, U2.7 (NRST)
unnamed: Boost1.1 (FREQ_SYNC), Rt1.1
unnamed: Boost1.3 (ILIMIT), Rilim1.1
unnamed: Boost1.4 (COMP), Rcomp1.1
unnamed: Boost1.5 (FB), Rfbb2.1, Rfbt2.2
unnamed: Boost1.7 (SW), Cboot1.1, L1.2
unnamed: Boost1.9 (DISDRV), Cgate1.2, M3.4 (G), Rgate1.2
unnamed: Boost1.10 (VCC), Cvcc1.1
unnamed: Boost1.13 (BST), Cboot1.2
unnamed: Buck1.1 (BOOT), Cboot_2.1
unnamed: Buck1.3 (PH), Cboot_2.2, L2.1
unnamed: Buck1.5 (VSENSE), Ccomp_3.2, Rfbb1.1, Rfbt1.2
unnamed: Buck1.6 (COMP), Ccomp_2.1, Rcomp2.1
unnamed: Buck1.7 (EN), Renb1.1, Rent1.2
unnamed: Buck1.8 (SS), Css1.1
unnamed: C2.1, R3.2, Y1.3
unnamed: C3.1, FB1.2, U1.3 (VI)
unnamed: Ccomp_1.1, Rcomp2.2
unnamed: Ccomp_4.1, Rcomp1.2
unnamed: D1.1 (K), R2.1
unnamed: D2.1 (K), R5.1
unnamed: D3.1 (K), R6.1
unnamed: D4.1 (K), R7.1
unnamed: J2.2, R4.2
unnamed: Boost1.8 (VOUT), Cgate1.1, Cout1.1, Cout2.1, M3.5 (D_1), M3.6 (D_2), M3.7 (D_3), M3.8 (D_4), M3.9 (D_5), M3.10 (D_6), M3.11 (D_7), Rgate1.1
unnamed: R1.1, SW1.2 (B)
SPI1_CS: J9.8, U2.20 (PA4)
SPI1_DC: J9.3, U2.25 (PC5)
SPI1_MISO: J9.6, U2.22 (PA6)
SPI1_MOSI: J9.5, U2.23 (PA7)
SPI1_RESET: J9.4, U2.24 (PC4)
SPI1_SCK: J9.7, U2.21 (PA5)
SWCLK: J2.4, U2.49 (PA14)
SWDIO: R4.1, U2.46 (PA13)
SWO: J2.6, U2.17 (PA3)
TIM2_CH1: J5.1, U2.14 (PA0)
UART4_RX: J4.5, U2.52 (PC11)
UART4_TX: J4.4, U2.51 (PC10)
UART5_RX: J3.5, U2.54 (PD2)
UART5_TX: J3.4, U2.53 (PC12)
USB_CONN_D+: J1.3 (D+), U3.3 (I/O2)
USB_CONN_D-: J1.2 (D-), U3.1 (I/O1)
USB_D+: U2.45 (PA12), U3.4 (I/O2)
USB_D-: U2.44 (PA11), U3.6 (I/O1)

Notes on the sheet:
Battery Voltage Monitor Connector
To Micro Power
Debugger Connector
VOC Sensor Connectors
Buck Convertor
Boost Convertor
USB and Regulator
Display Connector
Mounting holes with pads grounded
Power to microchip Can be powered by buck or USB
PM2.5 Sensor Connectors
To power sensors
Connection to battery/charger
Fan Connector
STM32 Microcontroller
